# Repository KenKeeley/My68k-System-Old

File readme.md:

# My Motorola 680x0 home built computer system.

My68k System is a home built Motorola 680x0 based small computer project. It is made in the style of vintage computers of the mid
to late 1970's and early 1980's using a mix of classic and modern technologies. The My68k System is made up of a mainboard provding
basic input, output, memory and storage functions along with several expansion cards connected via expansion slots that are loosely
based on the VME standard although using card edge connectors.

The purpose of the My68k System is to entertain through education. It is intended to be used to teach and promote principles of
electronic computer design. It is a solely non-profit educational project and is not intended for any commercial application.
The My68k System and related peripherals would be ideal as a small project to teach basic computer hardware and software
principles.

#### SOFTWARE USED
- [FreeCAD](https://www.freecadweb.org/)
- [KiCad](http://kicad-pcb.org/)
- [KiCad StepUp](https://github.com/easyw/kicadStepUpMod/)
- [Quartus II Web Edition](https://fpgasoftware.intel.com/13.1/)

Please report any issues and/or bugs via the "Issues" section on github.
If you have any extra reference material then please submit it via the "Issues" section on github.

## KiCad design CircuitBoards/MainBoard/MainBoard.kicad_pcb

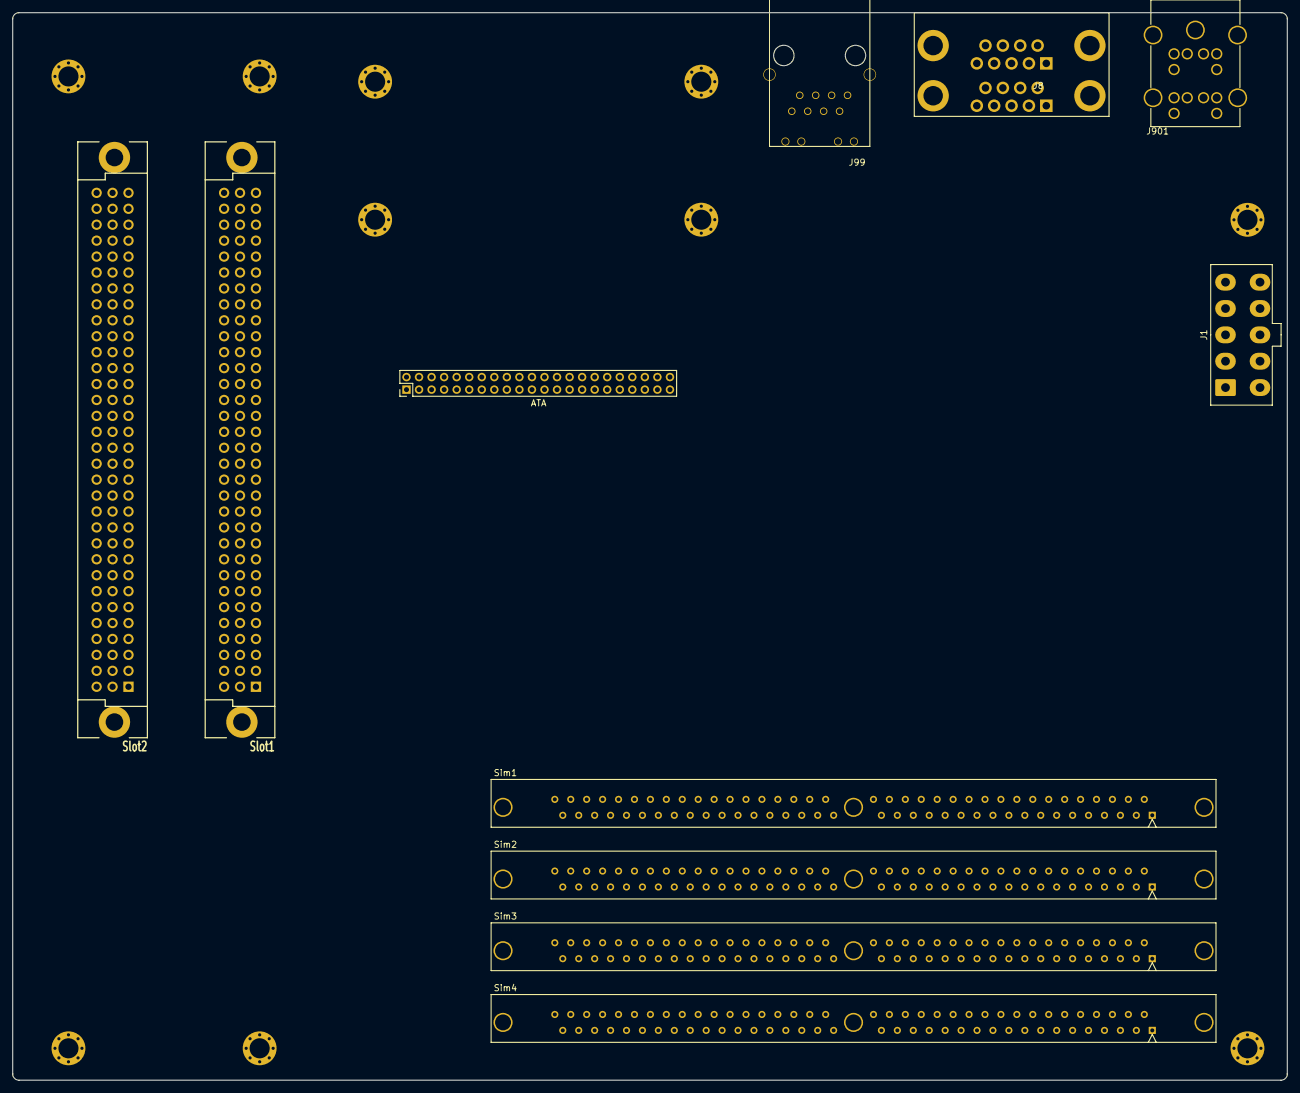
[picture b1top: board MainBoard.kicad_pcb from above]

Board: 2 copper layers, 203.2 x 170.2 mm, 21 parts (0 on the bottom side), 111 nets, no tracks yet.

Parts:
J1: 39-28-1103
J8: 178-009-613
J29: ATA; 87758-4416
J99: 5-2301994-2
J901: DualMiniDin6; KMDGX-6S-6S-S4N
MH1, MH2, MH3, MH4, MH5, MH6, MH7, MH8, MH9, MH10: Mounting_Hole_M3
Sim1, Sim2, Sim3, Sim4: Simm72; 5822021-4
Slot1, Slot2: DIN41612-C-96-F

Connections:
+5V: J1.1, J1.2, J1.3, J1.4, J29.41, J29.42, Sim1.10, Sim1.30, Sim1.59, Sim2.10, Sim2.30, Sim2.59, Sim3.10, Sim3.30, Sim3.59, Sim4.10, Sim4.30, Sim4.59, Slot1.A32, Slot1.B32, Slot1.C32, Slot2.A32, Slot2.B32, Slot2.C32
/DRAM Controller/nRAS0: Sim1.34, Sim1.44
/DRAM Controller/nRAS1: Sim1.33, Sim1.45
/Expansion Slot 2/nBGIN: Slot1.A21, Slot2.A20
/Expansion Slot 2/nIACKIN: Slot1.B21, Slot2.B20
/Simm Slot 2/nRAS0: Sim2.34, Sim2.44
/Simm Slot 2/nRAS1: Sim2.33, Sim2.45
/Simm Slot 3/nRAS0: Sim3.34, Sim3.44
/Simm Slot 3/nRAS1: Sim3.33, Sim3.45
/Simm Slot 4/nRAS0: Sim4.34, Sim4.44
/Simm Slot 4/nRAS1: Sim4.33, Sim4.45
A0: Slot1.A24, Slot2.A24
A0_DRAM: Sim1.12, Sim2.12, Sim3.12, Sim4.12
A1: J29.33, Slot1.A25, Slot2.A25
A1_DRAM: Sim1.13, Sim2.13, Sim3.13, Sim4.13
A2: J29.35, Slot1.A26, Slot2.A26
A2_DRAM: Sim1.14, Sim2.14, Sim3.14, Sim4.14
A3: J29.36, Slot1.A27, Slot2.A27
A3_DRAM: Sim1.15, Sim2.15, Sim3.15, Sim4.15
A4: Slot1.A28, Slot2.A28
A4_DRAM: Sim1.16, Sim2.16, Sim3.16, Sim4.16
A5: Slot1.A29, Slot2.A29
A5_DRAM: Sim1.17, Sim2.17, Sim3.17, Sim4.17
A6: Slot1.A30, Slot2.A30
A6_DRAM: Sim1.18, Sim2.18, Sim3.18, Sim4.18
A7: Slot1.A31, Slot2.A31
A7_DRAM: Sim1.28, Sim2.28, Sim3.28, Sim4.28
A8: Slot1.C24, Slot2.C24
A8_DRAM: Sim1.31, Sim2.31, Sim3.31, Sim4.31
A9: Slot1.C25, Slot2.C25
A9_DRAM: Sim1.32, Sim2.32, Sim3.32, Sim4.32
A10: Slot1.C26, Slot2.C26
A10_DRAM: Sim1.19, Sim2.19, Sim3.19, Sim4.19
A11: Slot1.C27, Slot2.C27
A11_DRAM: Sim1.29, Sim2.29, Sim3.29, Sim4.29
A12: Slot1.C28, Slot2.C28
A13: Slot1.C29, Slot2.C29
A14: Slot1.C30, Slot2.C30
A15: Slot1.C31, Slot2.C31
A16: Slot1.C11, Slot2.C11
A17: Slot1.C12, Slot2.C12
A18: Slot1.C13, Slot2.C13
A19: Slot1.C14, Slot2.C14
A20: Slot1.C15, Slot2.C15
A21: Slot1.C16, Slot2.C16
A22: Slot1.C17, Slot2.C17
A23: Slot1.C18, Slot2.C18
A24: Slot1.C19, Slot2.C19
A25: Slot1.A13, Slot2.A13
A26: Slot1.A14, Slot2.A14
A27: Slot1.A15, Slot2.A15
A28: Slot1.A16, Slot2.A16
A29: Slot1.A17, Slot2.A17
A30: Slot1.A18, Slot2.A18
A31: Slot1.A19, Slot2.A19
D0: Sim1.2, Sim2.2, Sim3.2, Sim4.2, Slot1.A1, Slot2.A1
D1: Sim1.4, Sim2.4, Sim3.4, Sim4.4, Slot1.A2, Slot2.A2
D2: Sim1.6, Sim2.6, Sim3.6, Sim4.6, Slot1.A3, Slot2.A3
D3: Sim1.8, Sim2.8, Sim3.8, Sim4.8, Slot1.A4, Slot2.A4
D4: Sim1.20, Sim2.20, Sim3.20, Sim4.20, Slot1.A5, Slot2.A5
D5: Sim1.22, Sim2.22, Sim3.22, Sim4.22, Slot1.A6, Slot2.A6
D6: Sim1.24, Sim2.24, Sim3.24, Sim4.24, Slot1.A7, Slot2.A7
D7: Sim1.26, Sim2.26, Sim3.26, Sim4.26, Slot1.A8, Slot2.A8
D8: Sim1.49, Sim2.49, Sim3.49, Sim4.49, Slot1.C1, Slot2.C1
D9: Sim1.51, Sim2.51, Sim3.51, Sim4.51, Slot1.C2, Slot2.C2
D10: Sim1.53, Sim2.53, Sim3.53, Sim4.53, Slot1.C3, Slot2.C3
D11: Sim1.55, Sim2.55, Sim3.55, Sim4.55, Slot1.C4, Slot2.C4
D12: Sim1.57, Sim2.57, Sim3.57, Sim4.57, Slot1.C5, Slot2.C5
D13: Sim1.61, Sim2.61, Sim3.61, Sim4.61, Slot1.C6, Slot2.C6
D14: Sim1.63, Sim2.63, Sim3.63, Sim4.63, Slot1.C7, Slot2.C7
D15: Sim1.65, Sim2.65, Sim3.65, Sim4.65, Slot1.C8, Slot2.C8
D16: Sim1.3, Sim2.3, Sim3.3, Sim4.3, Slot1.B1, Slot2.B1
D17: Sim1.5, Sim2.5, Sim3.5, Sim4.5, Slot1.B2, Slot2.B2
D18: Sim1.7, Sim2.7, Sim3.7, Sim4.7, Slot1.B3, Slot2.B3
D19: Sim1.9, Sim2.9, Sim3.9, Sim4.9, Slot1.B4, Slot2.B4
D20: Sim1.21, Sim2.21, Sim3.21, Sim4.21, Slot1.B5, Slot2.B5
D21: Sim1.23, Sim1.64, Sim2.23, Sim2.64, Sim3.23, Sim3.64, Sim4.23, Sim4.64, Slot1.B6, Slot2.B6
D22: Sim1.25, Sim2.25, Sim3.25, Sim4.25, Slot1.B7, Slot2.B7
D23: Sim1.27, Sim2.27, Sim3.27, Sim4.27, Slot1.B8, Slot2.B8
D24: Sim1.50, Sim2.50, Sim3.50, Sim4.50, Slot1.B11, Slot2.B11
D25: Sim1.52, Sim2.52, Sim3.52, Sim4.52, Slot1.B12, Slot2.B12
D26: Sim1.54, Sim2.54, Sim3.54, Sim4.54, Slot1.B13, Slot2.B13
D27: Sim1.56, Sim2.56, Sim3.56, Sim4.56, Slot1.B14, Slot2.B14
D28: Sim1.58, Sim2.58, Sim3.58, Sim4.58, Slot1.B15, Slot2.B15
D29: Sim1.60, Sim2.60, Sim3.60, Sim4.60, Slot1.B16, Slot2.B16
D30: Sim1.62, Sim2.62, Sim3.62, Sim4.62, Slot1.B17, Slot2.B17
D31: Slot1.B18, Slot2.B18
GND: J1.6, J1.7, J1.8, J1.9, J8.5A, J8.5B, J29.2, J29.19, J29.22, J29.24, J29.26, J29.30, J29.40, J29.43, J99.R4, J99.R5, J901.A3, J901.B3, J901.SH1, MH1.1, MH2.1, MH3.1, MH4.1, MH5.1, MH6.1, MH7.1, MH8.1, MH9.1, MH10.1, Sim1.1, Sim1.39, Sim1.72, Sim2.1, Sim2.39, Sim2.72, Sim3.1, Sim3.39, Sim3.72, Sim4.1, Sim4.39, Sim4.72, Slot1.33, Slot1.34, Slot1.A10, Slot1.A22, Slot1.B10, Slot1.B22, Slot1.C10, Slot1.C22, Slot2.33, Slot2.34, Slot2.A10, Slot2.A22, Slot2.B10, Slot2.B22, Slot2.C10, Slot2.C22
SIZ0: Slot1.A11, Slot2.A11
SIZ1: Slot1.A12, Slot2.A12
nAS: Slot1.B9, Slot2.B9
nBGACK: Slot1.A23, Slot2.A23
nBR: Slot1.C23, Slot2.C23
nCAS0: Sim1.40, Sim2.40, Sim3.40, Sim4.40
nCAS1: Sim1.43, Sim2.43, Sim3.43, Sim4.43
nCAS2: Sim1.41, Sim2.41, Sim3.41, Sim4.41
nCAS3: Sim1.42, Sim2.42, Sim3.42, Sim4.42
nDSACK0: Slot1.B23, Slot2.B23
nDSACK1: Slot1.B24, Slot2.B24
nHalt: Slot1.C20, Slot2.C20
nIRQ1: Slot1.B31, Slot2.B31
nIRQ2: Slot1.B30, Slot2.B30
nIRQ3: Slot1.B29, Slot2.B29
nIRQ4: Slot1.B28, Slot2.B28
nIRQ5: Slot1.B27, Slot2.B27
nIRQ6: Slot1.B26, Slot2.B26
nIRQ7: Slot1.B25, Slot2.B25
nReset: J29.1, Slot1.C9, Slot2.C9
nSTERM: Slot1.B19, Slot2.B19
nWE_DRAM: Sim1.47, Sim2.47, Sim3.47, Sim4.47
nWR: J29.23, Slot1.A9, Slot2.A9

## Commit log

2021-07-30 Initial creation of the Project
2021-08-02 Initial MainBoard creation
2021-08-03 MainBoard: Addition of the expansion slots
2021-08-03 MainBoard: Addition of the Decoder schematic
2021-08-03 MainBoard: Addition of the Support schematic
2021-08-03 MainBoard: Addition of the CPU schematic
2021-08-05 MainBoard: Addition of the Memory schematic
2021-08-05 MainBoard: Addition of the FPU schematic
2021-08-11 MainBoard: Addition of the DUART schematic
2021-08-13 MainBoard: Addition of the ATA schematic
2021-08-17 MainBoard: Addition of the RTC schematic
2021-08-18 MainBoard: Addition of the PS2 schematic
2021-08-19 MainBoard: Addition of the DRAM schematics
2021-08-20 MainBoard: Updating of the Power schematic
2021-08-27 MainBoard: Addition of the Network schematic
2021-09-02 MainBoard: Support CPLD design started
2021-09-06 MainBoard - Support CPLD: Address decoder added
2021-09-09 MainBoard - Support CPLD: DTACK and Watchdog timer added
2021-09-10 MainBoard - Support CPLD: Interrupts and IACK added
2021-09-21 MainBoard: DRAM Controller CPLD design added
